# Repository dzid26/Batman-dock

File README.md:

- KiCad 9
    - [Fabrication plugin](https://github.com/bennymeg/Fabrication-Toolkit)
- FreeCAD 1.1
    - Use [exportProject.FCMacro](https://gist.github.com/dzid26/e0ff365de43cabe658df9d93b92d1954) to quickly export step files with a macro
    - KiStepUp plugin to export `PCB_Sketch_master.stp` to Kicad and import part positions from Kicad

The design accounts for windshield curvature (R=4m). Although in hindsight this is not very useful as it translates to only 0.08mm surface delta for the batman width. The 3d printer can do it, but bigger effects might be even due to part warping and flex.

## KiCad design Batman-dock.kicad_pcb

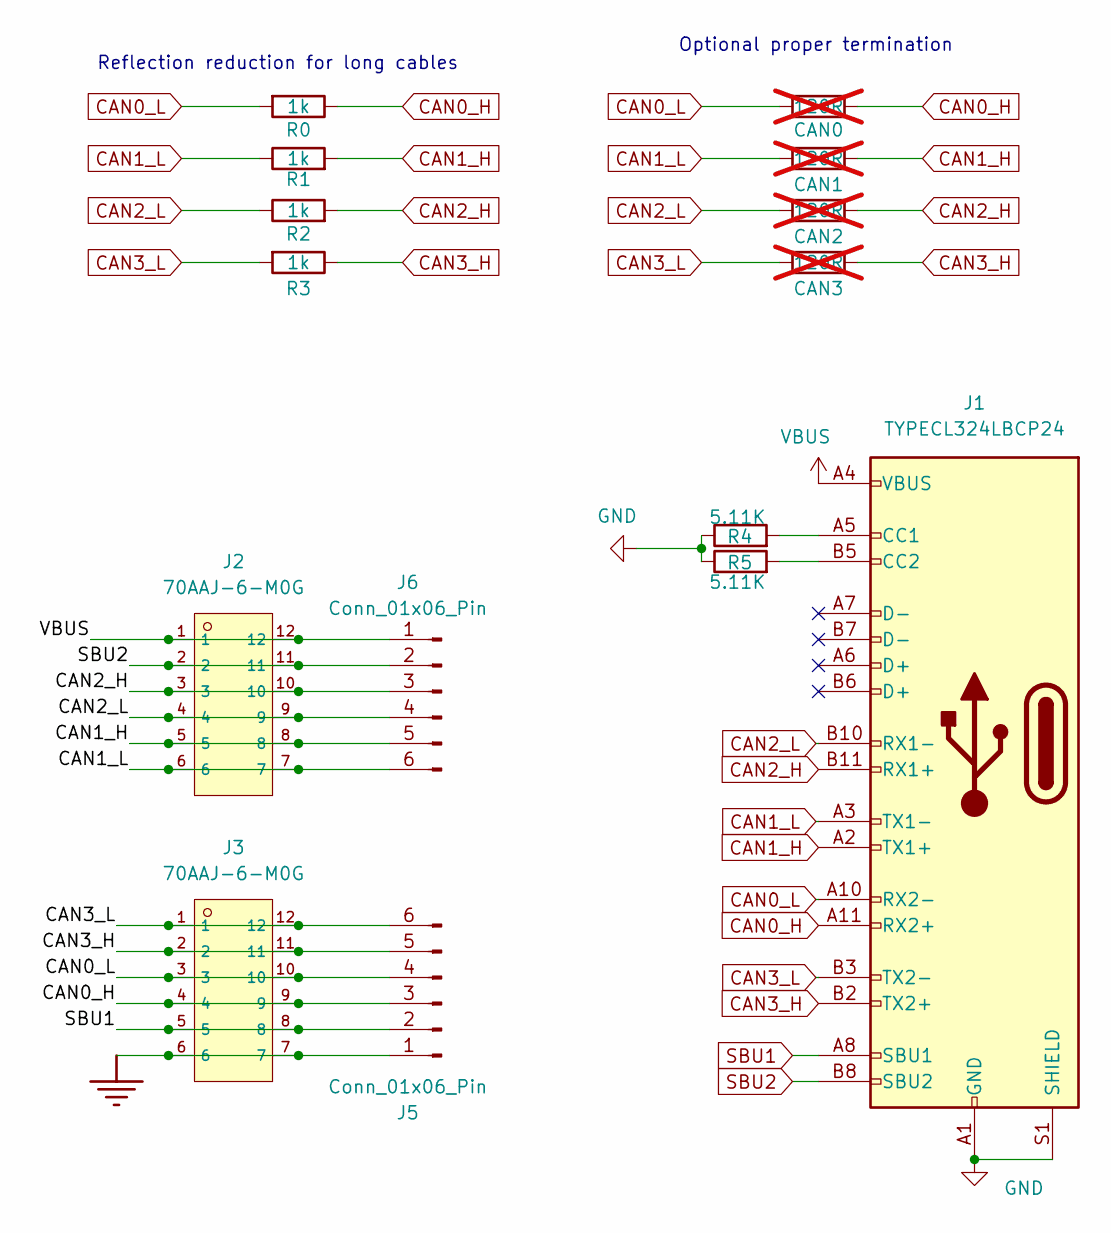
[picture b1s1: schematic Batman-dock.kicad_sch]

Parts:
CAN0, CAN1, CAN2, CAN3: 120R; R_1206_3216Metric_Pad1.30x1.75mm_HandSolder; not fitted
J1: TYPECL324LBCP24; USB-SMD_HC-TYPE-C-24P-CP1.0-5A-L10.45-01; LCSC C5345938
J2, J3: 70AAJ-6-M0G; CONN-SMD_12P-P2.54_70AAJ-6-M0G; LCSC C5137163
J5, J6: Conn_01x06_Pin; PinHeader_1x06_P2.54mm_Vertical
R0, R1, R2, R3: 1k; R_0603_1608Metric
R4, R5: 5.11K; R_0402_1005Metric; LCSC Part # C25905

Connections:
CAN0_H: CAN0.1, J1.A11 (RX2+), J3.4, J3.9, J5.3, R0.1
CAN0_L: CAN0.2, J1.A10 (RX2-), J3.3, J3.10, J5.4, R0.2
CAN1_H: CAN1.1, J1.A2 (TX1+), J2.5, J2.8, J6.5, R1.2
CAN1_L: CAN1.2, J1.A3 (TX1-), J2.6, J2.7, J6.6, R1.1
CAN2_H: CAN2.1, J1.B11 (RX1+), J2.3, J2.10, J6.3, R2.2
CAN2_L: CAN2.2, J1.B10 (RX1-), J2.4, J2.9, J6.4, R2.1
CAN3_H: CAN3.1, J1.B2 (TX2+), J3.2, J3.11, J5.5, R3.1
CAN3_L: CAN3.2, J1.B3 (TX2-), J3.1, J3.12, J5.6, R3.2
GND: J1.A1 (GND), J1.A12 (GND), J1.B1 (GND), J1.B12 (GND), J1.S1 (SHIELD), J3.6, J3.7, J5.1, R4.1, R5.1
unnamed: J1.A5 (CC1), R4.2
unnamed: J1.B5 (CC2), R5.2
SBU1: J1.A8 (SBU1), J3.5, J3.8, J5.2
SBU2: J1.B8 (SBU2), J2.2, J2.11, J6.2
VBUS: J1.A4 (VBUS), J1.A9 (VBUS), J1.B4 (VBUS), J1.B9 (VBUS), J2.1, J2.12, J6.1

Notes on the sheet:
Optional proper termination
Reflection reduction for long cables

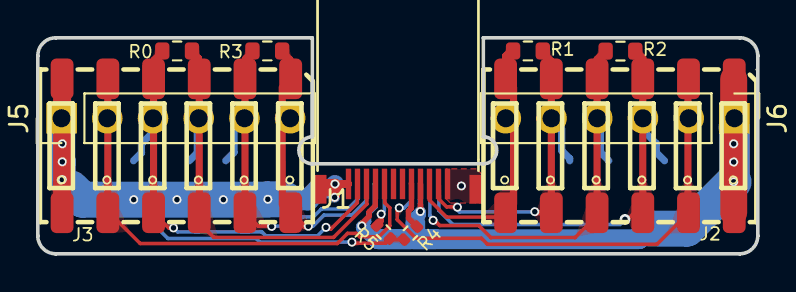
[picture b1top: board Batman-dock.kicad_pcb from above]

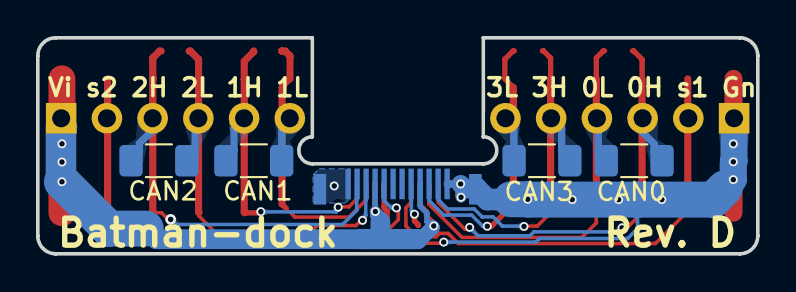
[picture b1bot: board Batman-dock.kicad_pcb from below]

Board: 2 copper layers, 40.0 x 12.0 mm, 15 parts (4 on the bottom side), 14 nets.

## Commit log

2025-03-03 Intitail Batman dock
2025-03-04 Kicad 9. Added usb and spring footprint.
2025-03-04 Shield
2025-03-07 Batman routing
2025-03-07 batman more clearance
2025-03-08 1mm batman PCB
2025-03-11 Batman sliding backplate
2025-03-13 20mm wide
2025-03-14 backplate tolerance and interlock
2025-03-14 reinforcement
2025-03-15 back insert slot and refinments
2025-03-15 USB-C backplate cutout
2025-03-17 refined design, insert interlock front/back, added crappy 8deg
2025-03-17 interlock masking
2025-03-17 picture
2025-03-17 end slot tolerance
2025-03-17 enlarged usb-c cutout
2025-03-17 rounded facade
2025-03-21 Added simple and simple 8deg batmans
2025-03-23 Added windshield curvature (miniscule), interlock geometry optimizations
2025-04-21 Added 3deg version. Optimized USB-C hole, and bridge for printing.
2025-04-21 Make space for 0402 resistors. 3deg to 4deg.
2025-04-21 Fixed CAN order RX<->TX flip. Less copper.
2025-04-21 Shorter PCB: 42mm -> 40mm
2025-04-23 Backplate push on PCB. Backplate insertion tolerance.
2025-04-26 thicker ground
2025-04-26 Flipped USB so it's "placed on top"
2025-05-07 more tolerance for interlocks - easier insertion
2025-05-09 Added simple 4deg batman Good for BMW E series with more "vertical" windshield
2025-05-09 Note on windshield curvature, hah
2025-06-22 Fixed 70AAJ-6-M0G name
2025-07-05 Rev.D added anti-reflection resistors and termination footprints. Added through hole test points
2025-08-10 -4deg batman and 4deg spacers
2025-08-12 Disable document compression
2025-08-22 PCB remarks and DNP
2025-11-03 Dock adapter WIP
